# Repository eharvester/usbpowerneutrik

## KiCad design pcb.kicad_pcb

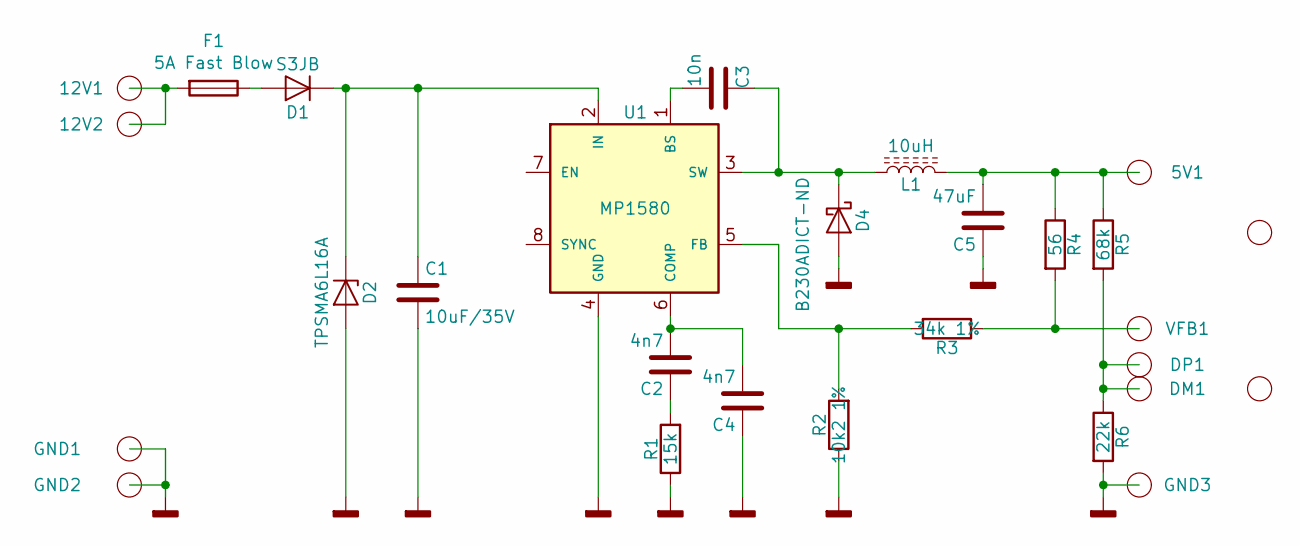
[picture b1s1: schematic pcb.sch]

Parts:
5V1: TEST_1P; VIA-0.8-1.6x2.5sq
12V1, 12V2: TEST_1P; VIA-1.2-2.5MM
C1: 10uF/35V; C_1206
C2, C4: 4n7; C_0603
C3: 10n; C_0603
C5: 47uF; C_0805
D1: S3JB; D_SMB
D2: TPSMA6L16A; D_SMA
D4: B230ADICT-ND; D_SMB
DM1: TEST_1P; VIA-0.8-1.6x2.5sq
DP1: TEST_1P; VIA-0.8-1.6x2.5sq
F1: 5A Fast Blow; LittleFuse Fast Fuse Axial
GND1, GND2, GND3: TEST_1P; VIA-1.2-2.5MM
L1: 10uH; L_Taiyo-Yuden_NR10050
R1: 15k; R_0603
R2: 10k2 1%; R_0603
R3: 34k 1%; R_0603
R4: 56; R_0603
R5: 68k; R_0603
R6: 22k; R_0603
U1: MP1580; SOIC-8_3.9x4.9mm_Pitch1.27mm
U4, U5: VIA; VIA-0.6MM-1.6MM
VFB1: TEST_1P; VIA-0.8-1.6x2.5sq

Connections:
GNDD: C1.2, C4.1, C5.1, D2.2 (A), D4.2 (A), GND1.1, GND2.1, GND3.1, R1.1, R2.1, R6.2, U1.4 (GND)
unnamed: 5V1.1, C5.2, L1.2, R4.1, R5.1
unnamed: 12V1.1, 12V2.1, F1.2
unnamed: C1.1, D1.1 (K), D2.1 (K), U1.2 (IN)
unnamed: C2.1, R1.2
unnamed: C2.2, C4.2, U1.6 (COMP)
unnamed: C3.1, D4.1 (K), L1.1, U1.3 (SW)
unnamed: C3.2, U1.1 (BS)
unnamed: D1.2 (A), F1.1
unnamed: DM1.1, DP1.1, R5.2, R6.1
unnamed: R2.2, R3.2, U1.5 (FB)
unnamed: R3.1, R4.2, VFB1.1

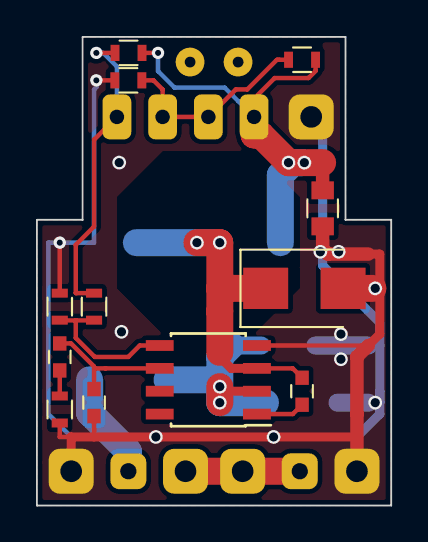
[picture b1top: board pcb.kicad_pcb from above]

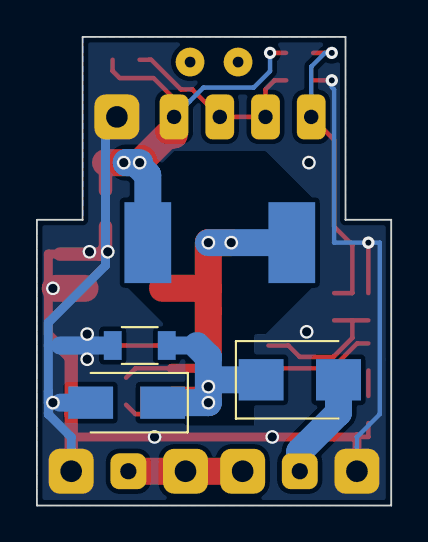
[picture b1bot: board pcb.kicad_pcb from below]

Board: 2 copper layers, 19.7 x 26.0 mm, 28 parts (4 on the bottom side), 12 nets.

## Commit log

2018-12-08 component values updated
